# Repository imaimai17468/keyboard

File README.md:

# keyboard

自作キーボード制作用リポジトリ。

## 仕様

| パーツ | 仕様 | 状態 |
| --- | --- | --- |
| キーキャップ | 黒、刻印は彫りのみ（インク充填なし） | 決定 |
| 基板 | JLCPCB で色を試す（まずは白・黒） | 検討中 |
| ケース | シルバー | 決定 |

### 基板の色（JLCPCB）

JLCPCB で選べるソルダーマスクの色は、緑・青・赤・黒・白・紫・黄の7色。2層基板ならほとんどの場合、色による追加料金はない。発注前に見積もり画面で確認する。

シルク（文字）の色は基板の色で決まる。

| 基板の色 | シルクの色 |
| --- | --- |
| 白 | 黒 |
| 緑・青・赤・黄・黒 | 白 |

試す候補:

- [ ] 白（シルバーのケースに合わせて明るめ）
- [ ] 黒（黒のキーキャップに合わせて締める）

参考:

- [Solder Mask Colors（JLCPCB Blog）](https://jlcpcb.com/blog/pcb-solder-mask-colors-performance)
- [PCB Color（JLCPCB FAQ）](https://jlcpcb.com/quote/pcbOrderFaq/PCB%20Color)

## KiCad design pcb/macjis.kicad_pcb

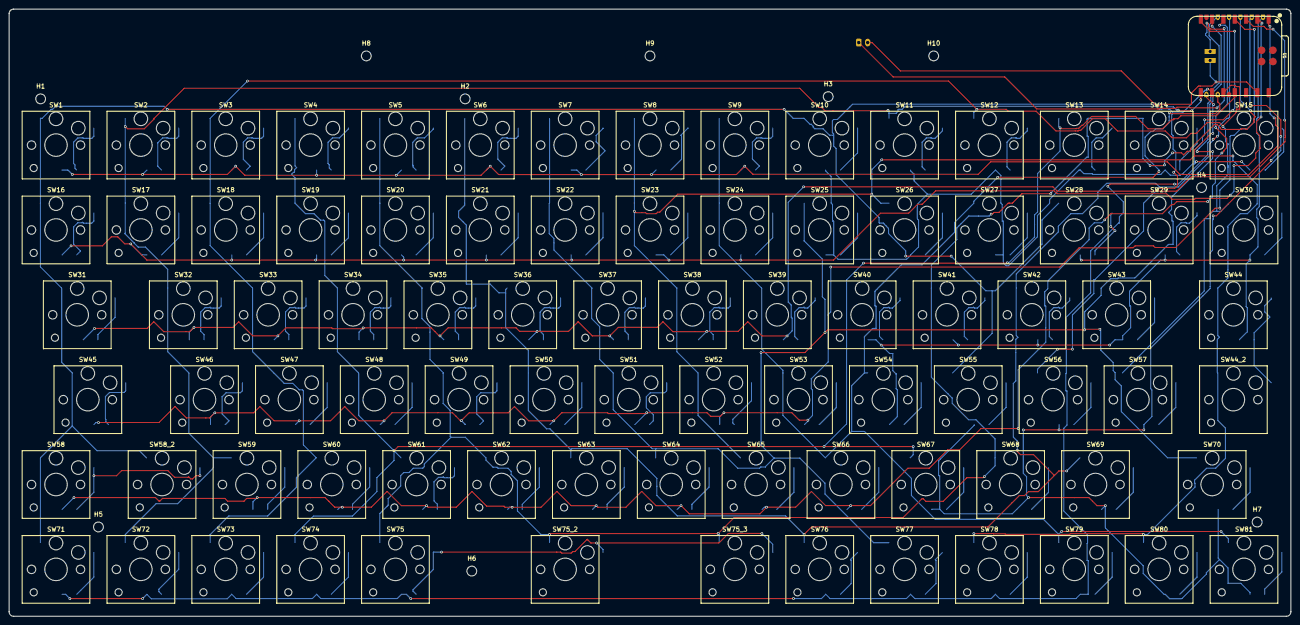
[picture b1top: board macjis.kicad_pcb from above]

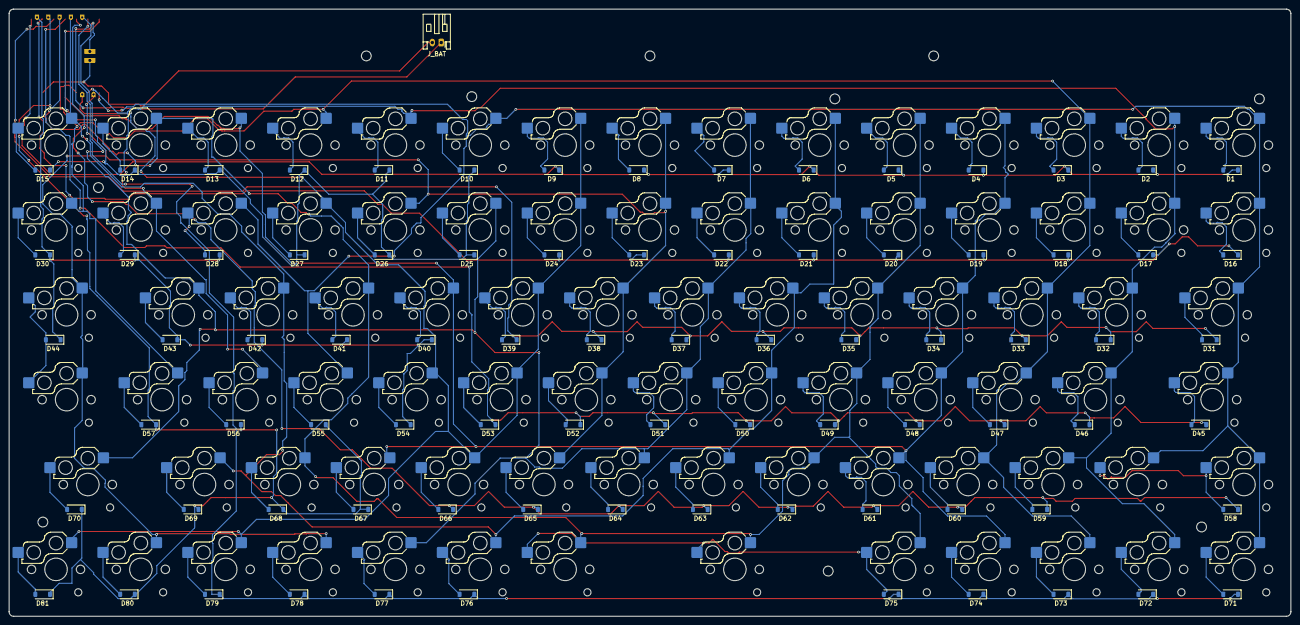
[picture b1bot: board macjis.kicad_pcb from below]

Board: 2 copper layers, 287.8 x 136.3 mm, 178 parts (82 on the bottom side), 101 nets.

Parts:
D1, D2, D3, D4, D5, D6, D7, D8, D9, D10, D11, D12, D13, D14, D15, D16, D17, D18, D19, D20, D21, D22, D23, D24, D25, D26, D27, D28, D29, D30, D31, D32, D33, D34, D35, D36, D37, D38, D39, D40, D41, D42, D43, D44, D45, D46, D47, D48, D49, D50, D51, D52, D53, D54, D55, D56, D57, D58, D59, D60, D61, D62, D63, D64, D65, D66, D67, D68, D69, D70, D71, D72, D73, D74, D75, D76, D77, D78, D79, D80, D81: D_SOD-123
H1, H2, H3, H4, H5, H6, H7, H8, H9, H10: MountingHole_2.2mm_M2_ISO14580
J_BAT: JST_PH_S2B-PH-K_1x02_P2.00mm_Horizontal
SW1, SW2, SW3, SW4, SW5, SW6, SW7, SW8, SW9, SW10, SW11, SW12, SW13, SW14, SW15, SW16, SW17, SW18, SW19, SW20, SW21, SW22, SW23, SW24, SW25, SW26, SW27, SW28, SW29, SW30, SW31, SW32, SW33, SW34, SW35, SW36, SW37, SW38, SW39, SW40, SW41, SW42, SW43, SW44, SW44_2, SW45, SW46, SW47, SW48, SW49, SW50, SW51, SW52, SW53, SW54, SW55, SW56, SW57, SW58, SW58_2, SW59, SW60, SW61, SW62, SW63, SW64, SW65, SW66, SW67, SW68, SW69, SW70, SW71, SW72, SW73, SW74, SW75, SW75_2, SW75_3, SW76, SW77, SW78, SW79, SW80, SW81: SW_Hotswap_Kailh_Choc_V1V2
U1: XIAO-nRF52840-Plus-SMD

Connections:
BAT+: J_BAT.1, U1.28
COL0: SW1.1, SW10.1, SW16.1, SW28.1, SW31.1, SW45.1, SW55.1, SW58.1, SW58_2.1, SW71.1, U1.8
COL1: SW2.1, SW11.1, SW17.1, SW29.1, SW32.1, SW46.1, SW56.1, SW59.1, SW72.1, U1.9
COL2: SW3.1, SW12.1, SW18.1, SW30.1, SW33.1, SW47.1, SW57.1, SW60.1, SW73.1, U1.10
COL3: SW4.1, SW13.1, SW19.1, SW34.1, SW40.1, SW48.1, SW61.1, SW67.1, SW74.1, U1.11
COL4: SW5.1, SW14.1, SW20.1, SW35.1, SW41.1, SW49.1, SW62.1, SW68.1, SW75.1, SW75_2.1, SW75_3.1, U1.17
COL5: SW6.1, SW15.1, SW21.1, SW36.1, SW42.1, SW50.1, SW63.1, SW69.1, SW76.1, U1.18
COL6: SW7.1, SW22.1, SW25.1, SW37.1, SW43.1, SW51.1, SW64.1, SW70.1, SW77.1, U1.19
COL7: SW8.1, SW23.1, SW26.1, SW38.1, SW44.1, SW44_2.1, SW52.1, SW65.1, SW78.1, SW80.1, U1.21
COL8: SW9.1, SW24.1, SW27.1, SW39.1, SW53.1, SW54.1, SW66.1, SW79.1, SW81.1, U1.22
GND: J_BAT.2, U1.13, U1.29
ROW0: D1.1, D2.1, D3.1, D4.1, D5.1, D6.1, D7.1, D8.1, D9.1, U1.1
ROW1: D16.1, D17.1, D18.1, D19.1, D20.1, D21.1, D22.1, D23.1, D24.1, U1.2
ROW2: D31.1, D32.1, D33.1, D34.1, D35.1, D36.1, D37.1, D38.1, D39.1, U1.3
ROW3: D45.1, D46.1, D47.1, D48.1, D49.1, D50.1, D51.1, D52.1, D53.1, U1.4
ROW4: D58.1, D59.1, D60.1, D61.1, D62.1, D63.1, D64.1, D65.1, D66.1, U1.5
ROW5: D71.1, D72.1, D73.1, D74.1, D75.1, D76.1, D77.1, D78.1, D79.1, U1.6
ROW6: D10.1, D11.1, D12.1, D13.1, D14.1, D15.1, D25.1, D26.1, D27.1, U1.7
ROW7: D28.1, D29.1, D30.1, D40.1, D41.1, D42.1, D43.1, D44.1, D54.1, U1.15
ROW8: D55.1, D56.1, D57.1, D67.1, D68.1, D69.1, D70.1, D80.1, D81.1, U1.16
SW1_D: D1.2, SW1.2
SW2_D: D2.2, SW2.2
SW3_D: D3.2, SW3.2
SW4_D: D4.2, SW4.2
SW5_D: D5.2, SW5.2
SW6_D: D6.2, SW6.2
SW7_D: D7.2, SW7.2
SW8_D: D8.2, SW8.2
SW9_D: D9.2, SW9.2
SW10_D: D10.2, SW10.2
SW11_D: D11.2, SW11.2
SW12_D: D12.2, SW12.2
SW13_D: D13.2, SW13.2
SW14_D: D14.2, SW14.2
SW15_D: D15.2, SW15.2
SW16_D: D16.2, SW16.2
SW17_D: D17.2, SW17.2
SW18_D: D18.2, SW18.2
SW19_D: D19.2, SW19.2
SW20_D: D20.2, SW20.2
SW21_D: D21.2, SW21.2
SW22_D: D22.2, SW22.2
SW23_D: D23.2, SW23.2
SW24_D: D24.2, SW24.2
SW25_D: D25.2, SW25.2
SW26_D: D26.2, SW26.2
SW27_D: D27.2, SW27.2
SW28_D: D28.2, SW28.2
SW29_D: D29.2, SW29.2
SW30_D: D30.2, SW30.2
SW31_D: D31.2, SW31.2
SW32_D: D32.2, SW32.2
SW33_D: D33.2, SW33.2
SW34_D: D34.2, SW34.2
SW35_D: D35.2, SW35.2
SW36_D: D36.2, SW36.2
SW37_D: D37.2, SW37.2
SW38_D: D38.2, SW38.2
SW39_D: D39.2, SW39.2
SW40_D: D40.2, SW40.2
SW41_D: D41.2, SW41.2
SW42_D: D42.2, SW42.2
SW43_D: D43.2, SW43.2
SW44_D: D44.2, SW44.2, SW44_2.2
SW45_D: D45.2, SW45.2
SW46_D: D46.2, SW46.2
SW47_D: D47.2, SW47.2
SW48_D: D48.2, SW48.2
SW49_D: D49.2, SW49.2
SW50_D: D50.2, SW50.2
SW51_D: D51.2, SW51.2
SW52_D: D52.2, SW52.2
SW53_D: D53.2, SW53.2
SW54_D: D54.2, SW54.2
SW55_D: D55.2, SW55.2
SW56_D: D56.2, SW56.2
SW57_D: D57.2, SW57.2
SW58_D: D58.2, SW58.2, SW58_2.2
SW59_D: D59.2, SW59.2
SW60_D: D60.2, SW60.2
SW61_D: D61.2, SW61.2
SW62_D: D62.2, SW62.2
SW63_D: D63.2, SW63.2
SW64_D: D64.2, SW64.2
SW65_D: D65.2, SW65.2
SW66_D: D66.2, SW66.2
SW67_D: D67.2, SW67.2
SW68_D: D68.2, SW68.2
SW69_D: D69.2, SW69.2
SW70_D: D70.2, SW70.2
SW71_D: D71.2, SW71.2
SW72_D: D72.2, SW72.2
SW73_D: D73.2, SW73.2
SW74_D: D74.2, SW74.2
SW75_D: D75.2, SW75.2, SW75_2.2, SW75_3.2
SW76_D: D76.2, SW76.2
SW77_D: D77.2, SW77.2
SW78_D: D78.2, SW78.2
SW79_D: D79.2, SW79.2
SW80_D: D80.2, SW80.2
SW81_D: D81.2, SW81.2

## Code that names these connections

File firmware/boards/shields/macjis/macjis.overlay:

/* scripts/gen_zmk.py で生成。直接編集しない */

#include <dt-bindings/zmk/matrix_transform.h>
#include <physical_layouts.dtsi>

/ {
    chosen {
        zmk,kscan = &kscan0;
        zmk,physical-layout = &macjis_layout;
    };

    kscan0: kscan {
        compatible = "zmk,kscan-gpio-matrix";
        wakeup-source;
        diode-direction = "col2row";

        row-gpios
            = <&gpio0 2 (GPIO_ACTIVE_HIGH | GPIO_PULL_DOWN)>  /* ROW0 = D0 */
            , <&gpio0 3 (GPIO_ACTIVE_HIGH | GPIO_PULL_DOWN)>  /* ROW1 = D1 */
            , <&gpio0 28 (GPIO_ACTIVE_HIGH | GPIO_PULL_DOWN)>  /* ROW2 = D2 */
            , <&gpio0 29 (GPIO_ACTIVE_HIGH | GPIO_PULL_DOWN)>  /* ROW3 = D3 */
            , <&gpio0 4 (GPIO_ACTIVE_HIGH | GPIO_PULL_DOWN)>  /* ROW4 = D4 */
            , <&gpio0 5 (GPIO_ACTIVE_HIGH | GPIO_PULL_DOWN)>  /* ROW5 = D5 */
            , <&gpio1 11 (GPIO_ACTIVE_HIGH | GPIO_PULL_DOWN)>  /* ROW6 = D6 */
            , <&gpio0 15 (GPIO_ACTIVE_HIGH | GPIO_PULL_DOWN)>  /* ROW7 = D11 */
            , <&gpio0 19 (GPIO_ACTIVE_HIGH | GPIO_PULL_DOWN)>  /* ROW8 = D12 */
            ;
        col-gpios
            = <&gpio1 12 GPIO_ACTIVE_HIGH>  /* COL0 = D7 */
            , <&gpio1 13 GPIO_ACTIVE_HIGH>  /* COL1 = D8 */
            , <&gpio1 14 GPIO_ACTIVE_HIGH>  /* COL2 = D9 */
            , <&gpio1 15 GPIO_ACTIVE_HIGH>  /* COL3 = D10 */
            , <&gpio1 1 GPIO_ACTIVE_HIGH>  /* COL4 = D13 */
            , <&gpio0 9 GPIO_ACTIVE_HIGH>  /* COL5 = D14 */
            , <&gpio0 10 GPIO_ACTIVE_HIGH>  /* COL6 = D15 */
            , <&gpio1 7 GPIO_ACTIVE_HIGH>  /* COL7 = D17 */
            , <&gpio1 5 GPIO_ACTIVE_HIGH>  /* COL8 = D18 */
            ;
    };

    default_transform: keymap_transform_0 {
        compatible = "zmk,matrix-transform";
        rows = <9>;
        columns = <9>;
        map = <
RC(0,0) RC(0,1) RC(0,2) RC(0,3) RC(0,4) RC(0,5) RC(0,6) RC(0,7) RC(0,8) RC(6,0) RC(6,1) RC(6,2) RC(6,3) RC(6,4) RC(6,5)
RC(1,0) RC(1,1) RC(1,2) RC(1,3) RC(1,4) RC(1,5) RC(1,6) RC(1,7) RC(1,8) RC(6,6) RC(6,7) RC(6,8) RC(7,0) RC(7,1) RC(7,2)
RC(2,0) RC(2,1) RC(2,2) RC(2,3) RC(2,4) RC(2,5) RC(2,6) RC(2,7) RC(2,8) RC(7,3) RC(7,4) RC(7,5) RC(7,6) RC(7,7)
RC(3,0) RC(3,1) RC(3,2) RC(3,3) RC(3,4) RC(3,5) RC(3,6) RC(3,7) RC(3,8) RC(7,8) RC(8,0) RC(8,1) RC(8,2)
RC(4,0) RC(4,1) RC(4,2) RC(4,3) RC(4,4) RC(4,5) RC(4,6) RC(4,7) RC(4,8) RC(8,3) RC(8,4) RC(8,5) RC(8,6)
RC(5,0) RC(5,1) RC(5,2) RC(5,3) RC(5,4) RC(5,5) RC(5,6) RC(5,7) RC(5,8) RC(8,7) RC(8,8)
        >;
    };

    macjis_layout: macjis_layout {
        compatible = "zmk,physical-layout";
        display-name = "MacBook JIS 75%";
        transform = <&default_transform>;

        keys  //                     w   h    x   y  rot rx ry
            = <&key_physical_attrs 100 100    0   0 0 0 0>  /* esc */
            , <&key_physical_attrs 100 100  100   0 0 0 0>  /* F1 */
            , <&key_physical_attrs 100 100  200   0 0 0 0>  /* F2 */
            , <&key_physical_attrs 100 100  300   0 0 0 0>  /* F3 */
            , <&key_physical_attrs 100 100  400   0 0 0 0>  /* F4 */
            , <&key_physical_attrs 100 100  500   0 0 0 0>  /* F5 */
            , <&key_physical_attrs 100 100  600   0 0 0 0>  /* F6 */
            , <&key_physical_attrs 100 100  700   0 0 0 0>  /* F7 */
            , <&key_physical_attrs 100 100  800   0 0 0 0>  /* F8 */
            , <&key_physical_attrs 100 100  900   0 0 0 0>  /* F9 */
            , <&key_physical_attrs 100 100 1000   0 0 0 0>  /* F10 */
            , <&key_physical_attrs 100 100 1100   0 0 0 0>  /* F11 */
            , <&key_physical_attrs 100 100 1200   0 0 0 0>  /* F12 */
            , <&key_physical_attrs 100 100 1300   0 0 0 0>  /* lock */
            , <&key_physical_attrs 100 100 1400   0 0 0 0>  /* light */
            , <&key_physical_attrs 100 100    0 100 0 0 0>  /* 半角 */
            , <&key_physical_attrs 100 100  100 100 0 0 0>  /* 1 */
            , <&key_physical_attrs 100 100  200 100 0 0 0>  /* 2 */
            , <&key_physical_attrs 100 100  300 100 0 0 0>  /* 3 */
            , <&key_physical_attrs 100 100  400 100 0 0 0>  /* 4 */
            , <&key_physical_attrs 100 100  500 100 0 0 0>  /* 5 */
            , <&key_physical_attrs 100 100  600 100 0 0 0>  /* 6 */
            , <&key_physical_attrs 100 100  700 100 0 0 0>  /* 7 */
            , <&key_physical_attrs 100 100  800 100 0 0 0>  /* 8 */
            , <&key_physical_attrs 100 100  900 100 0 0 0>  /* 9 */
            , <&key_physical_attrs 100 100 1000 100 0 0 0>  /* 0 */
            , <&key_physical_attrs 100 100 1100 100 0 0 0>  /* - */
            , <&key_physical_attrs 100 100 1200 100 0 0 0>  /* ^ */
            , <&key_physical_attrs 100 100 1300 100 0 0 0>  /* ¥ */
            , <&key_physical_attrs 100 100 1400 100 0 0 0>  /* bs */
            , <&key_physical_attrs 150 100    0 200 0 0 0>  /* tab */
            , <&key_physical_attrs 100 100  150 200 0 0 0>  /* Q */
            , <&key_physical_attrs 100 100  250 200 0 0 0>  /* W */
            , <&key_physical_attrs 100 100  350 200 0 0 0>  /* E */
            , <&key_physical_attrs 100 100  450 200 0 0 0>  /* R */
            , <&key_physical_attrs 100 100  550 200 0 0 0>  /* T */
            , <&key_physical_attrs 100 100  650 200 0 0 0>  /* Y */
            , <&key_physical_attrs 100 100  750 200 0 0 0>  /* U */
            , <&key_physical_attrs 100 100  850 200 0 0 0>  /* I */
            , <&key_physical_attrs 100 100  950 200 0 0 0>  /* O */
            , <&key_physical_attrs 100 100 1050 200 0 0 0>  /* P */
            , <&key_physical_attrs 100 100 1150 200 0 0 0>  /* @ */
            , <&key_physical_attrs 100 100 1250 200 0 0 0>  /* [ */
            , <&key_physical_attrs 125 200 1375 200 0 0 0>  /* enter */
            , <&key_physical_attrs 175 100    0 300 0 0 0>  /* ctrl */
            , <&key_physical_attrs 100 100  175 300 0 0 0>  /* A */
            , <&key_physical_attrs 100 100  275 300 0 0 0>  /* S */
            , <&key_physical_attrs 100 100  375 300 0 0 0>  /* D */
            , <&key_physical_attrs 100 100  475 300 0 0 0>  /* F */
            , <&key_physical_attrs 100 100  575 300 0 0 0>  /* G */
            , <&key_physical_attrs 100 100  675 300 0 0 0>  /* H */
            , <&key_physical_attrs 100 100  775 300 0 0 0>  /* J */
            , <&key_physical_attrs 100 100  875 300 0 0 0>  /* K */
            , <&key_physical_attrs 100 100  975 300 0 0 0>  /* L */
            , <&key_physical_attrs 100 100 1075 300 0 0 0>  /* ; */
            , <&key_physical_attrs 100 100 1175 300 0 0 0>  /* : */
            , <&key_physical_attrs 100 100 1275 300 0 0 0>  /* ] */
            , <&key_physical_attrs 225 100    0 400 0 0 0>  /* shift */
            , <&key_physical_attrs 100 100  225 400 0 0 0>  /* Z */
            , <&key_physical_attrs 100 100  325 400 0 0 0>  /* X */
            , <&key_physical_attrs 100 100  425 400 0 0 0>  /* C */
            , <&key_physical_attrs 100 100  525 400 0 0 0>  /* V */
            , <&key_physical_attrs 100 100  625 400 0 0 0>  /* B */
            , <&key_physical_attrs 100 100  725 400 0 0 0>  /* N */
            , <&key_physical_attrs 100 100  825 400 0 0 0>  /* M */
            , <&key_physical_attrs 100 100  925 400 0 0 0>  /* , */
            , <&key_physical_attrs 100 100 1025 400 0 0 0>  /* . */
            , <&key_physical_attrs 100 100 1125 400 0 0 0>  /* / */
            , <&key_physical_attrs 100 100 1225 400 0 0 0>  /* _ */
            , <&key_physical_attrs 175 100 1325 400 0 0 0>  /* shift */
            , <&key_physical_attrs 100 100    0 500 0 0 0>  /* fn */
            , <&key_physical_attrs 100 100  100 500 0 0 0>  /* opt */
            , <&key_physical_attrs 100 100  200 500 0 0 0>  /* cmd */
            , <&key_physical_attrs 100 100  300 500 0 0 0>  /* 英数 */
            , <&key_physical_attrs 500 100  400 500 0 0 0>  /* space */
            , <&key_physical_attrs 100 100  900 500 0 0 0>  /* かな */
            , <&key_physical_attrs 100 100 1000 500 0 0 0>  /* cmd */
            , <&key_physical_attrs 100 100 1100 500 0 0 0>  /* ← */
            , <&key_physical_attrs 100 100 1200 500 0 0 0>  /* ↑ */
            , <&key_physical_attrs 100 100 1300 500 0 0 0>  /* ↓ */
            , <&key_physical_attrs 100 100 1400 500 0 0 0>  /* → */
            ;
    };
};

/ {
    /* 電源スイッチは無い。&soft_off で切り、キーを押すと復帰する（kscan を復帰元にする） */
    soft_off_wakers {
        compatible = "zmk,soft-off-wakeup-sources";
        wakeup-sources = <&kscan0>;
    };

};

/* 状態ランプは XIAO の 3 色 LED。zmk-rgbled-widget の rgbled_adapter シールドが割り当てる
   （build.yaml で shield に一緒に指定する） */

/* D14 (P0.09) / D15 (P0.10) は NFC 端子なので GPIO として使う設定にする */
&uicr {
    nfct-pins-as-gpios;
};
